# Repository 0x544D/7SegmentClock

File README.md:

# 7SegmentClock
Just a simple 7 segment clock 

* design based on ATtiny 2313
* features alarm clock mode

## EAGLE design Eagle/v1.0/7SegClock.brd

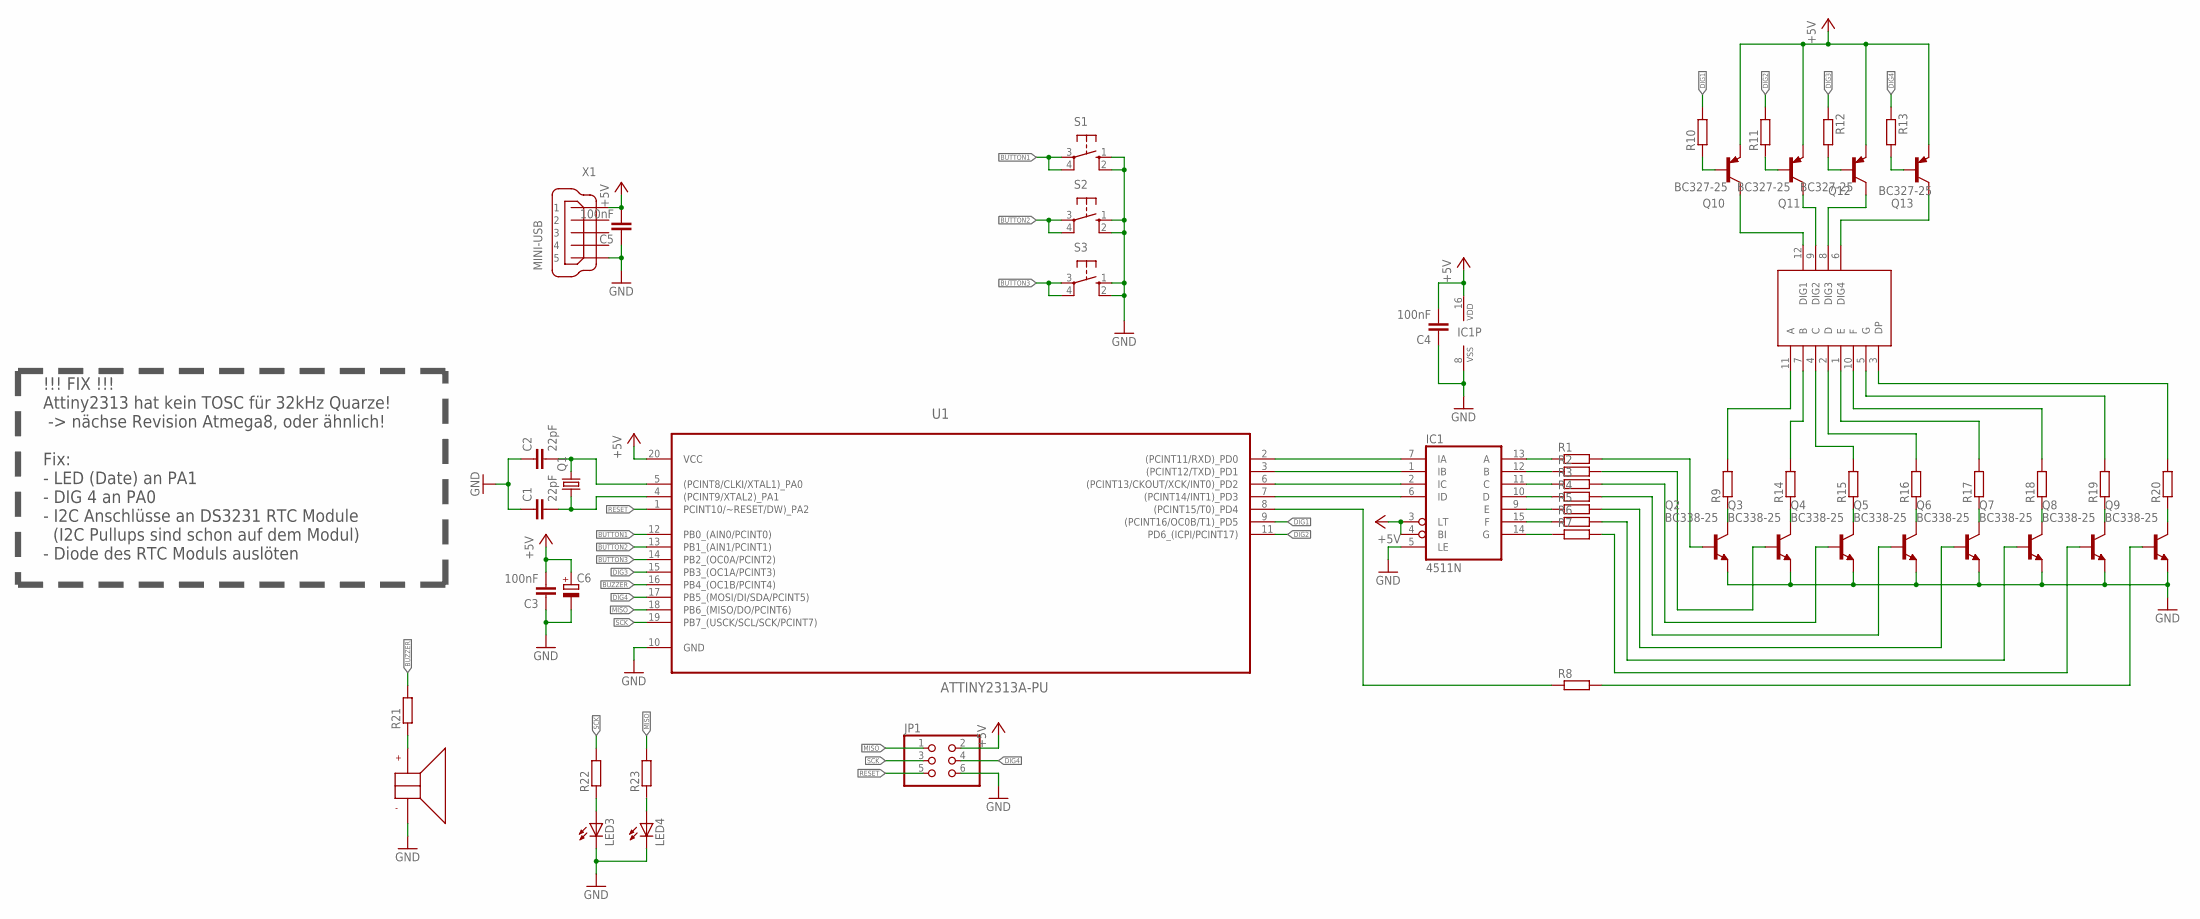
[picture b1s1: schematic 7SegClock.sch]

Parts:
C1, C2: 22pF; C025-025X050
C3, C4, C5: 100nF; C025-025X050
C6: CPOL-EUE2-5; E2-5
IC1: 4511N; DIL16
JP1: PINHD-2X3; 2X03
LED1: 7SEGCOMAN
LED3, LED4: LED3MM
Q1: CRYSTALTC38H; TC38H
Q2, Q3, Q4, Q5, Q6, Q7, Q8, Q9: BC338-25; TO92-EBC
Q10, Q11, Q12, Q13: BC327-25; TO92-EBC
R1, R2, R3, R4, R5, R6, R7, R8, R9, R10, R11, R12, R13, R14, R15, R16, R17, R18, R19, R20, R21, R22, R23: R-EU_0207/7; 0207/7
S1, S2, S3: 10-XX; B3F-10XX
U1: ATTINY2313A-PU; DIP254P762X533-20
U$1: PIEZO_BUZZER_RM7,6
X1: MINI-USB; 32005-201

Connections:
+5V: C3.2, C4.2, C5.2, C6.+, IC1.3 (LT), IC1.4 (BI), IC1.16 (VDD), JP1.2, Q10.E, Q11.E, Q12.E, Q13.E, U1.20 (VCC), X1.1
BUTTON1: S1.3, S1.4 (P1), U1.12 (PB0_(AIN0/PCINT0))
BUTTON2: S2.3, S2.4 (P1), U1.13 (PB1_(AIN1/PCINT1))
BUTTON3: S3.3, S3.4 (P1), U1.14 (PB2_(OC0A/PCINT2))
BUZZER: R21.2, U1.16 (PB4_(OC1B/PCINT4))
DIG1: R10.2, U1.9 ((PCINT16/OC0B/T1)_PD5)
DIG2: R11.2, U1.11 (PD6_(ICPI/PCINT17))
DIG3: R12.1, U1.15 (PB3_(OC1A/PCINT3))
DIG4: JP1.4, R13.1, U1.17 (PB5_(MOSI/DI/SDA/PCINT5))
GND: C1.1, C2.1, C3.1, C4.1, C5.1, C6.-, IC1.5 (LE), IC1.8 (VSS), JP1.6, LED3.K (C), LED4.K (C), Q2.E, Q3.E, Q4.E, Q5.E, Q6.E, Q7.E, Q8.E, Q9.E, S1.1 (S), S1.2 (S1), S2.1 (S), S2.2 (S1), S3.1 (S), S3.2 (S1), U1.10 (GND), U$1.P$2, X1.5
MISO: JP1.1, R23.2, U1.18 (PB6_(MISO/DO/PCINT6))
unnamed: C2.2, Q1.2, U1.5 ((PCINT8/CLKI/XTAL1)_PA0)
unnamed: C1.2, Q1.1, U1.4 ((PCINT9/XTAL2)_PA1)
unnamed: Q2.B, R1.2
unnamed: Q3.B, R2.2
unnamed: Q4.B, R3.2
unnamed: Q5.B, R4.2
unnamed: Q6.B, R5.2
unnamed: Q7.B, R6.2
unnamed: Q8.B, R7.2
unnamed: IC1.7 (IA), U1.2 ((PCINT11/RXD)_PD0)
unnamed: IC1.1 (IB), U1.3 ((PCINT12/TXD)_PD1)
unnamed: IC1.2 (IC), U1.6 ((PCINT13/CKOUT/XCK/INT0)_PD2)
unnamed: IC1.6 (ID), U1.7 ((PCINT14/INT1)_PD3)
unnamed: Q9.B, R8.2
unnamed: R8.1, U1.8 ((PCINT15/T0)_PD4)
unnamed: IC1.14 (G), R7.1
unnamed: IC1.15 (F), R6.1
unnamed: IC1.9 (E), R5.1
unnamed: IC1.10 (D), R4.1
unnamed: IC1.11 (C), R3.1
unnamed: IC1.12 (B), R2.1
unnamed: IC1.13 (A), R1.1
unnamed: LED1.11 (A), R9.2
unnamed: LED1.7 (B), R14.2
unnamed: LED1.4 (C), R15.2
unnamed: LED1.2 (D), R16.2
unnamed: LED1.1 (E), R17.2
unnamed: LED1.10 (F), R18.2
unnamed: LED1.5 (G), R19.2
unnamed: LED1.3 (DP), R20.2
unnamed: R21.1, U$1.P$1
unnamed: LED3.A, R22.1
unnamed: LED1.12 (DIG1), Q10.C
unnamed: LED1.9 (DIG2), Q11.C
unnamed: LED1.8 (DIG3), Q12.C
unnamed: LED1.6 (DIG4), Q13.C
unnamed: Q10.B, R10.1
unnamed: Q11.B, R11.1
unnamed: Q12.B, R12.2
unnamed: Q13.B, R13.2
unnamed: Q2.C, R9.1
unnamed: Q3.C, R14.1
unnamed: Q4.C, R15.1
unnamed: Q5.C, R16.1
unnamed: Q6.C, R17.1
unnamed: Q7.C, R18.1
unnamed: Q8.C, R19.1
unnamed: Q9.C, R20.1
unnamed: LED4.A, R23.1
RESET: JP1.5, U1.1 (PCINT10/~RESET/DW)_PA2)
SCK: JP1.3, R22.2, U1.19 (PB7_(USCK/SCL/SCK/PCINT7))

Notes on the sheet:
!!! FIX !!! Attiny2313 hat kein TOSC für 32kHz Quarze! -> nächse Revision Atmega8, oder ähnlich! Fix: - LED (Date) an PA1 - DIG 4 an PA0 - I2C Anschlüsse an DS3231 RTC Module (I2C Pullups sind schon auf dem Modul) - Diode des RTC Moduls auslöten

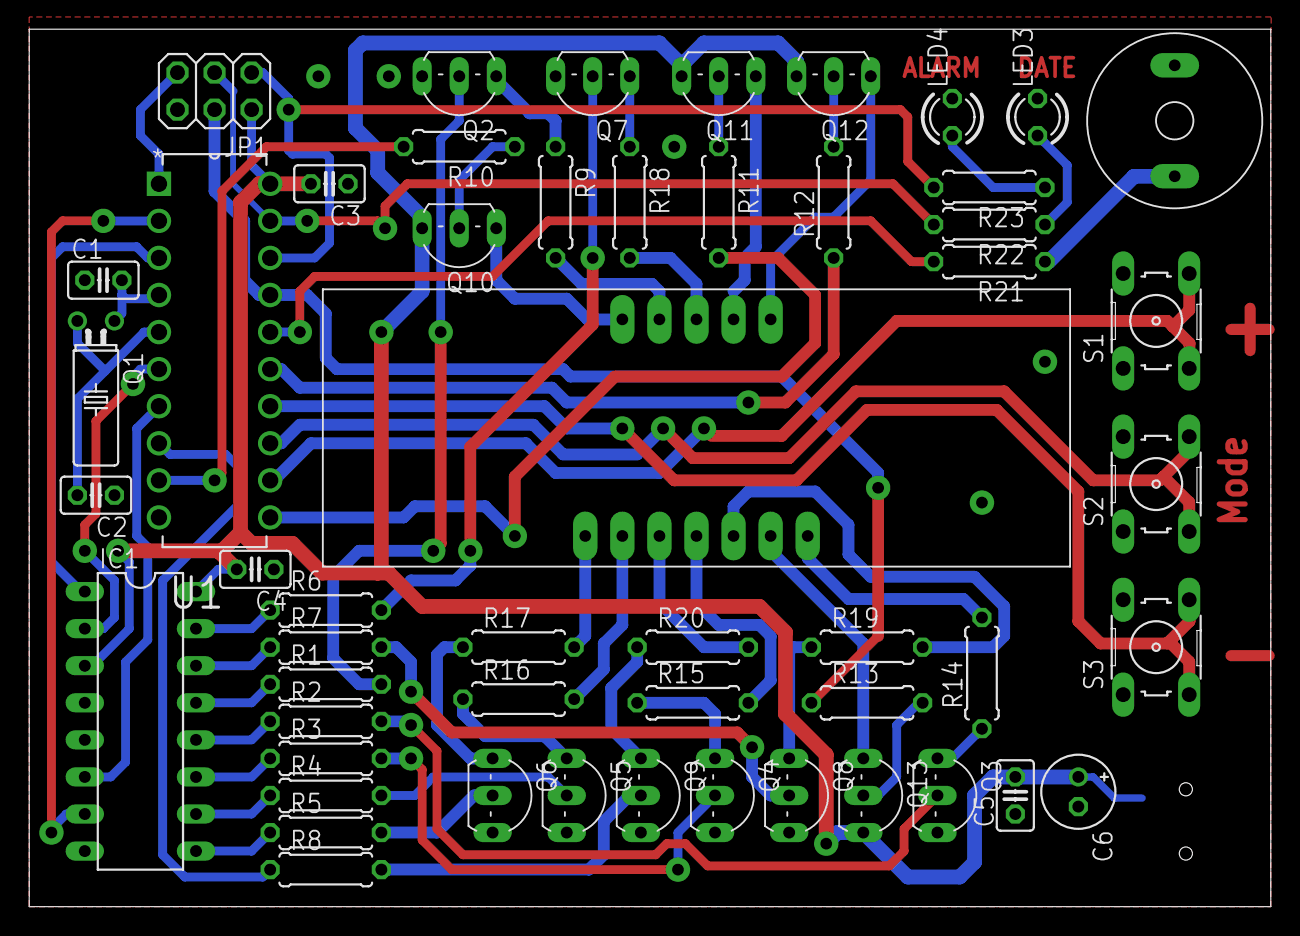
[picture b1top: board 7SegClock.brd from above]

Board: 2 copper layers, 85.1 x 60.1 mm, 53 parts (1 on the bottom side), 62 nets.

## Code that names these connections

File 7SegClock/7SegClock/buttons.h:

/*
 * buttons.h
 *
 * Created: 31.08.2015 15:26:11
 *  Author: Tobi
 */ 


#ifndef BUTTONS_H_
#define BUTTONS_H_

#ifdef __cplusplus
extern "C" {
#endif

// #define BUTTON1 0
// #define BUTTON2 1
// #define BUTTON3 2
// #define BUTTON4 3
// #define BUTTON5 4
// #define BUTTON6 5
// #define BUTTON7 6
// #define BUTTON8 7

/**
 * check if a key has been pressed. Each pressed key is reported
 * only once
 */
uint8_t get_key_press( uint8_t key_mask );


/**
 * check if a key has been pressed long enough such that the
 * key repeat functionality kicks in. After a small setup delay
 * the key is reported being pressed in subsequent calls
 * to this function. This simulates the user repeatedly
 * pressing and releasing the key
 */
uint8_t get_key_rpt( uint8_t key_mask );


/**
 * check if a key is pressed right now
 */
uint8_t get_key_state( uint8_t key_mask );


uint8_t get_key_short( uint8_t key_mask );
uint8_t get_key_long( uint8_t key_mask );




/**
 * @brief initializes buttons, uses Timer0 for debouncing purposes
 */
void init_buttons();


/**
 * @brief  checks if a button was pressed and saves the event.
 * needs to get called in main loop periodically
 */
void checkButtons();


#ifdef __cplusplus
}
#endif


#endif /* BUTTONS_H_ */

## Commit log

2018-07-08 initial commit, moved project from SVN to Github
